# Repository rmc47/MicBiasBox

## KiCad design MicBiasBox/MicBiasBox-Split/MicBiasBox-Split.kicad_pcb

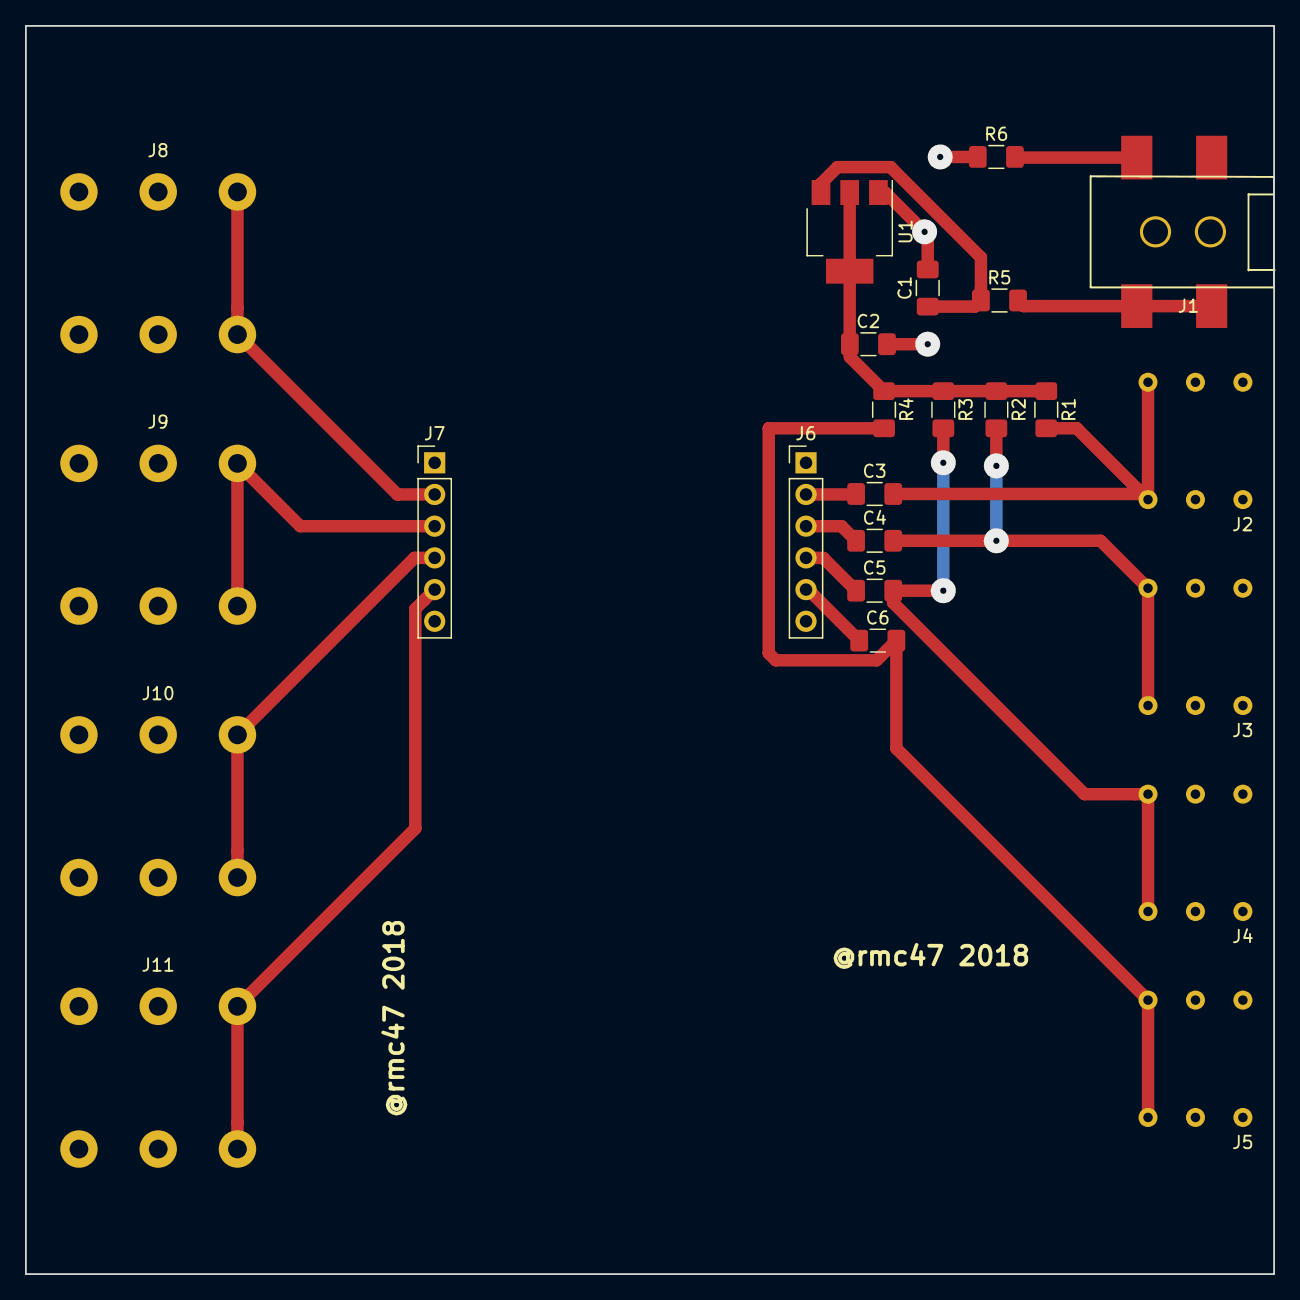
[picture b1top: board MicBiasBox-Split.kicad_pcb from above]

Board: 2 copper layers, 100.0 x 100.0 mm, 24 parts (0 on the bottom side), 18 nets.

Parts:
C1, C2, C3, C4, C5, C6: C; C_1206_3216Metric_Pad1.42x1.75mm_HandSolder
J1: Barrel_Jack; Cliff_FC68148S_2.1mm_DC_Jack_SMD
J2, J3, J4, J5: AudioJack3_Switch; Cliff_FCR1295_S9_BBB_3.5mm_Jack_Stereo
J6, J7: Conn_01x06_Male; PinHeader_1x06_P2.54mm_Vertical
J8, J9, J10, J11: AudioJack3_Switch; Amphenol_ACJS_MHDR_6.35mm_Jack
R1, R2, R3, R4: R; R_1206_3216Metric_Pad1.42x1.75mm_HandSolder
R5, R6: 0R; R_1206_3216Metric_Pad1.42x1.75mm_HandSolder
U1: LD1117S50TR_SOT223; SOT-223-3_TabPin2

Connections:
GND: C1.2, C2.2, J2.R, J2.RN, J2.S, J2.SN, J3.R, J3.RN, J3.S, J3.SN, J4.R, J4.RN, J4.S, J4.SN, J5.R, J5.RN, J5.S, J5.SN, J6.1, R6.1, U1.1
unnamed: C1.1, R5.1, U1.3
unnamed: C2.1, R1.1, R2.1, R3.1, R4.1, U1.2
unnamed: C3.1, J6.2
unnamed: C3.2, J2.T, J2.TN, R1.2
unnamed: C4.1, J6.3
unnamed: C4.2, J3.T, J3.TN, R2.2
unnamed: C5.1, J6.4
unnamed: C5.2, J4.T, J4.TN, R3.2
unnamed: C6.1, J6.5
unnamed: C6.2, J5.T, J5.TN, R4.2
unnamed: J1.1, R5.2
unnamed: J1.2, R6.2
unnamed: J7.2, J8.T, J8.TN
unnamed: J7.3, J9.T, J9.TN
unnamed: J7.1, J8.R, J8.RN, J8.S, J8.SN, J9.R, J9.RN, J9.S, J9.SN, J10.R, J10.RN, J10.S, J10.SN, J11.R, J11.RN, J11.S, J11.SN
unnamed: J7.4, J10.T, J10.TN
unnamed: J7.5, J11.T, J11.TN

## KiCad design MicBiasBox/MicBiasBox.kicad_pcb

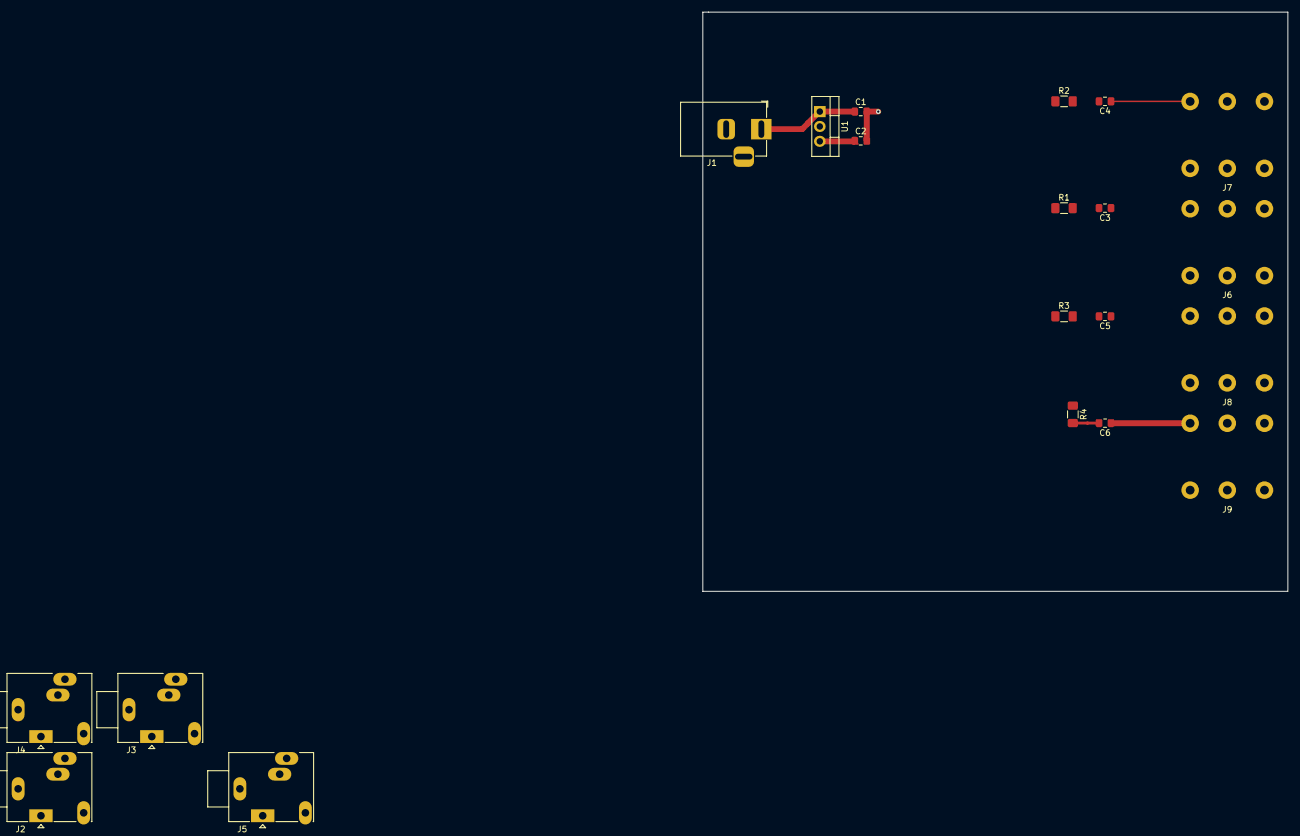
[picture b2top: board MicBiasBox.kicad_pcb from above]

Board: 2 copper layers, 100.0 x 99.0 mm, 20 parts (0 on the bottom side), 11 nets.

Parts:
C1, C2, C3, C4, C5, C6: C; C_0805_2012Metric_Pad1.15x1.40mm_HandSolder
J1: Barrel_Jack; BarrelJack_Horizontal
J2, J3, J4, J5: AudioJack3_Switch; StereoJack_3.5mm_Switch_Ledino_KB3SPRS_Horizontal
J6, J7, J8, J9: AudioJack3_Switch; Amphenol_ACJS_MHDR_6.35mm_Jack
R1, R2, R3, R4: R; R_1206_3216Metric_Pad1.42x1.75mm_HandSolder
U1: LM7805_TO220; TO-220-3_Vertical

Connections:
GND: C1.2, C2.2, J1.2, J6.R, J6.S, J7.R, J7.S, J8.R, J8.S, J9.R, J9.S, U1.2
unnamed: C1.1, J1.1, U1.1
unnamed: C2.1, R1.1, R2.1, R3.1, R4.1, U1.3
unnamed: C3.1, J6.T
unnamed: C3.2, R1.2
unnamed: C4.1, J7.T
unnamed: C4.2, R2.2
unnamed: C5.1, J8.T
unnamed: C5.2, R3.2
unnamed: C6.1, J9.T
unnamed: C6.2, R4.2

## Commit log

2018-12-02 First attempts
